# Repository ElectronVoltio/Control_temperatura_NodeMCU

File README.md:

# Control_temperatura_NodeMCU
Directorio con la ducumentación sobre el control de temperatura con NodeMCU y programado con Arduino

Video: https://youtu.be/zLw39d-6L_0

El esquema y la PCB están realizados con el Kicad

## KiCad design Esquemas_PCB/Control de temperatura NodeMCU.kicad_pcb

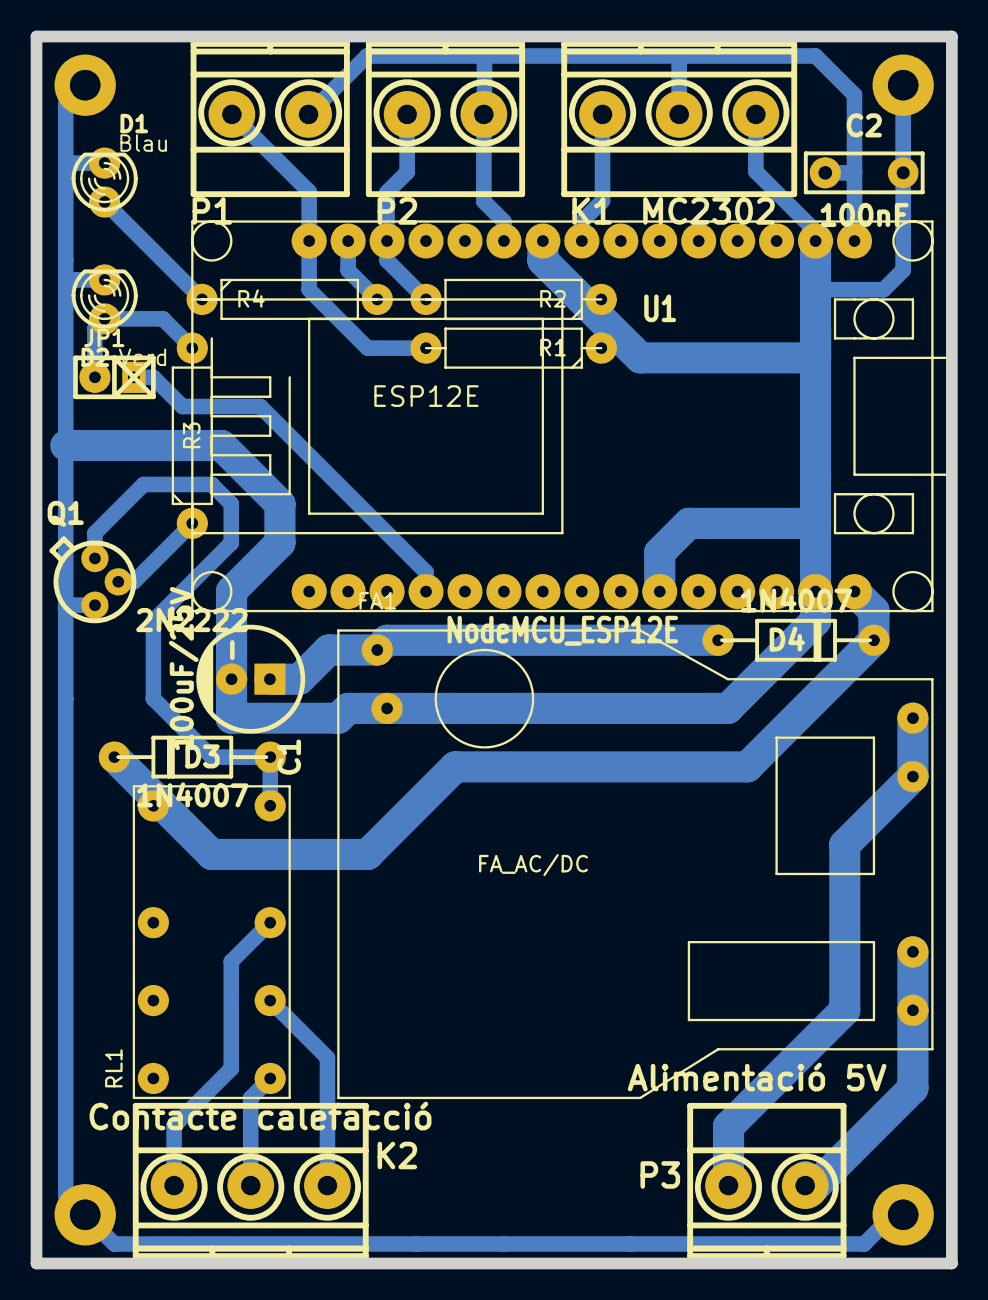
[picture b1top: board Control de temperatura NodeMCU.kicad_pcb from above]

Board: 2 copper layers, 59.7 x 80.0 mm, 20 parts (0 on the bottom side), 18 nets.

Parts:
C1: 100uF/25V; CP_6.3x11mm
C2: 100nF; cnp_7x2mm
D1: Blau; Led_3mm
D2: Verd; Led_3mm
D3, D4: 1N4007; diode_do41
FA1: FA_AC/DC; FA220_5Vdc
JP1: JUMPER; pin_socket_2
K1: MC2302; mkds_1,5-3
K2: Contacte calefacció; mkds_1,5-3
P1: Pulsador Activar/desactivar Calefacció; mkds_1,5-2
P2: Pulsador Encendre/apagar calefacció; mkds_1,5-2
P3: Alimentació 5V; mkds_1,5-2
Q1: 2N2222; to18
R1, R2, R4: 120; RC05
R3: 68; RC05
RL1: FINDER-30.22; Rele_30.22
U1: NodeMCU_ESP12E

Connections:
/3,3V: C2.1, K1.2, P1.1, P2.1, U1.16, U1.25
/AC1: FA1.1, P3.2
/AC2: FA1.2, P3.1
/Vcc_fa: C1.1, D4.1, FA1.3
GND: C1.2, C2.2, D1.2, D2.2, FA1.4, K1.1, Q1.1, R1.1, R2.1, U1.10, U1.14, U1.17, U1.24
unnamed: D1.1, R4.1
unnamed: D2.1, JP1.2, R3.2
unnamed: D3.1, Q1.3, RL1.2
unnamed: JP1.1, U1.4
unnamed: K1.3, U1.23
unnamed: K2.1, RL1.21
unnamed: K2.2, RL1.24
unnamed: K2.3, RL1.22
unnamed: P1.2, R1.2, U1.30
unnamed: P2.2, R2.2, U1.28
unnamed: Q1.2, R3.1
unnamed: R4.2, U1.29
VCC: D3.2, D4.2, RL1.1, U1.15

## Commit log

2018-01-06 Create Rearme
